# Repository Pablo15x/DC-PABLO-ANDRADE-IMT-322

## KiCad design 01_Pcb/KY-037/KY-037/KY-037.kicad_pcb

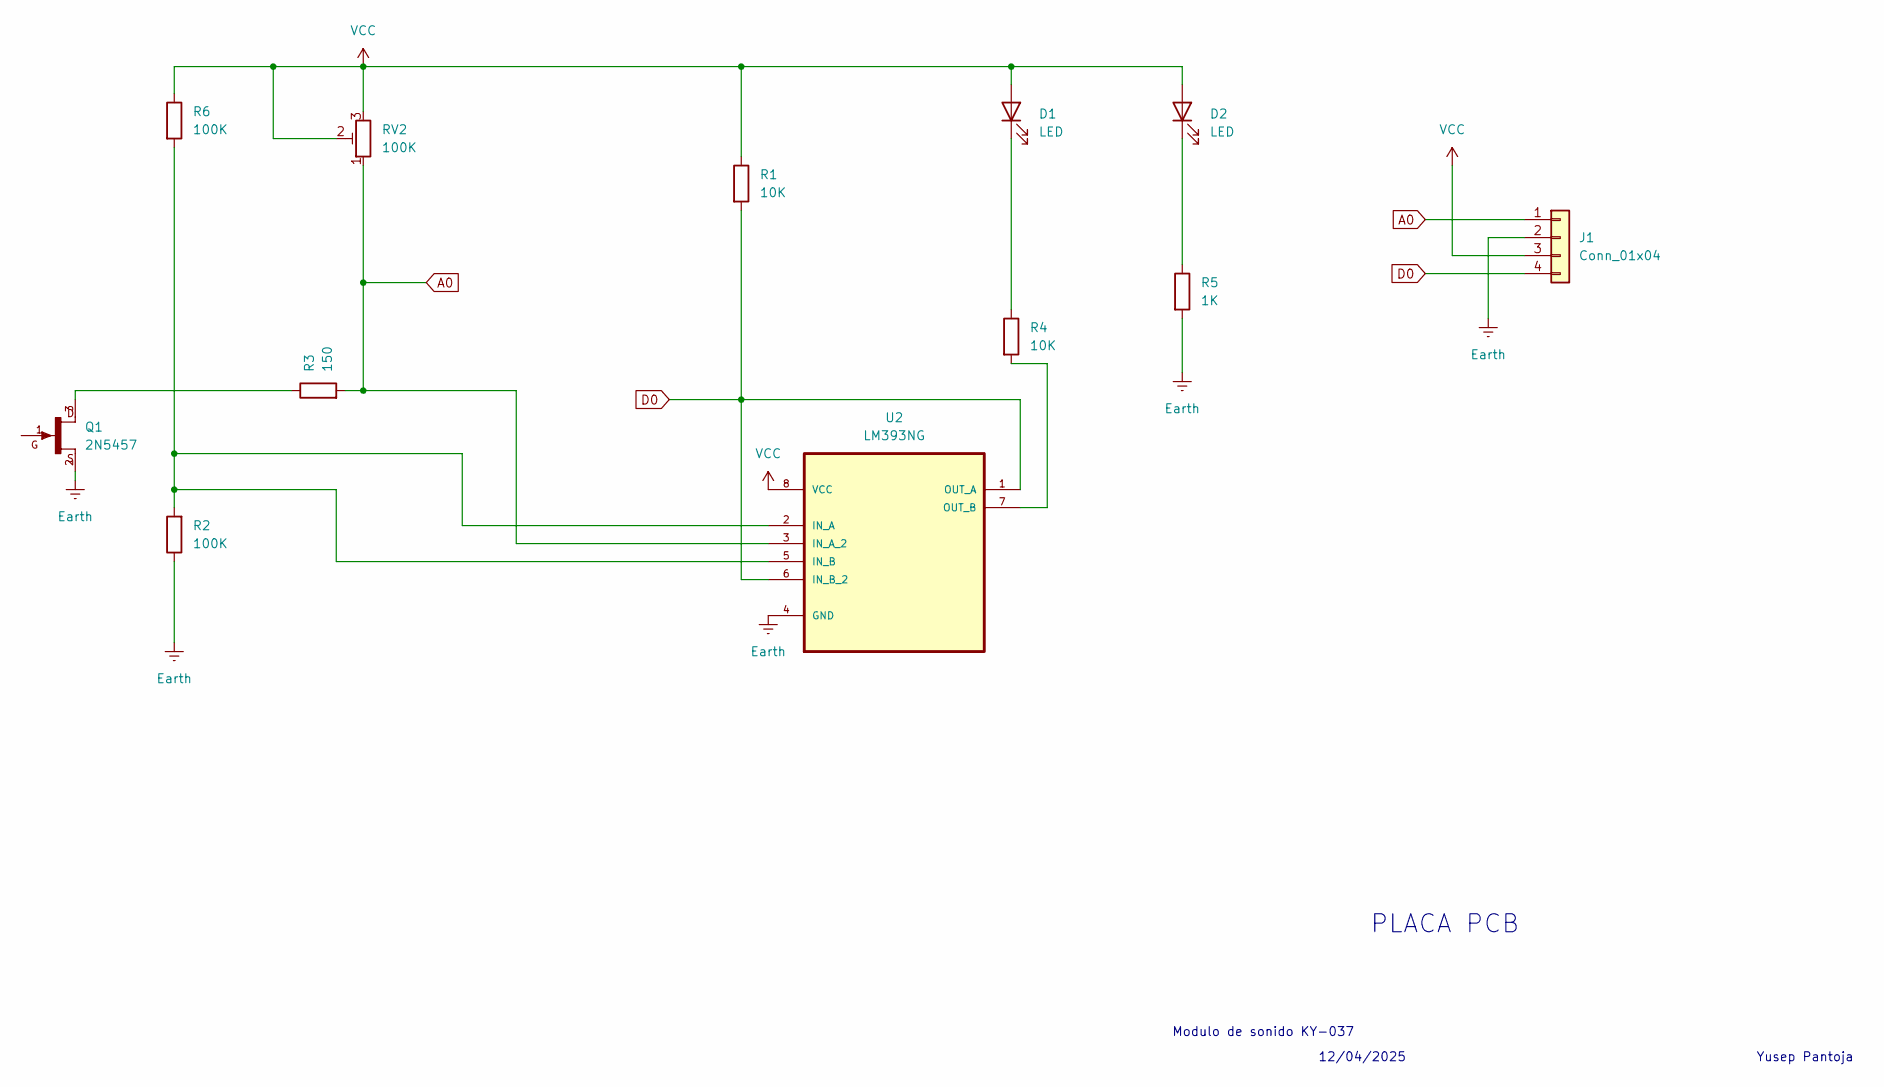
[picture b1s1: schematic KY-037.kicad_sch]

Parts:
D1, D2: LED; D_DO-35_SOD27_P7.62mm_Horizontal
J1: Conn_01x04; PinHeader_1x04_P2.54mm_Vertical
Q1: 2N5457; TO-92L_Inline
R1, R4: 10K; R_Axial_DIN0207_L6.3mm_D2.5mm_P7.62mm_Horizontal
R2, R6: 100K; R_Axial_DIN0207_L6.3mm_D2.5mm_P7.62mm_Horizontal
R3: 150; R_Axial_DIN0207_L6.3mm_D2.5mm_P7.62mm_Horizontal
R5: 1K; R_Axial_DIN0207_L6.3mm_D2.5mm_P7.62mm_Horizontal
RV2: 100K; Potentiometer_Bourns_3296W_Vertical
U2: LM393NG; CERDIP-8_W7.62mm_SideBrazed; MPN LM393NG

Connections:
A0: J1.1, R3.2, RV2.1, U2.3 (IN_A_2)
D0: J1.4, R1.2, U2.1 (OUT_A), U2.6 (IN_B_2)
Earth: J1.2, Q1.2, R2.1, R5.2, U2.4 (GND)
unnamed: D1.1 (K), R4.1
unnamed: D2.1 (K), R5.1
unnamed: Q1.3, R3.1
unnamed: R2.2, R6.2, U2.2 (IN_A), U2.5 (IN_B)
unnamed: R4.2, U2.7 (OUT_B)
VCC: D1.2 (A), D2.2 (A), J1.3, R1.1, R6.1, RV2.2, RV2.3, U2.8 (VCC)

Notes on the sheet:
PLACA PCB
12/04/2025
Modulo de sonido KY-037
Yusep Pantoja

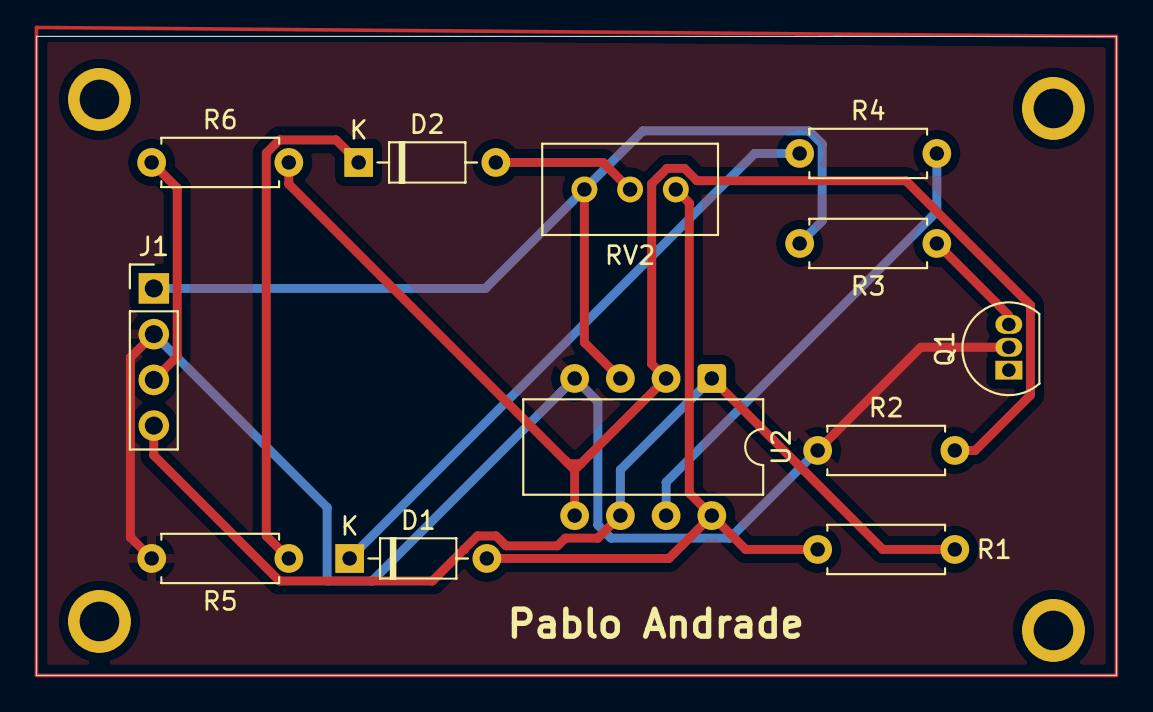
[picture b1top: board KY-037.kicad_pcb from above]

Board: 2 copper layers, 60.0 x 35.5 mm, 12 parts (0 on the bottom side), 9 nets.

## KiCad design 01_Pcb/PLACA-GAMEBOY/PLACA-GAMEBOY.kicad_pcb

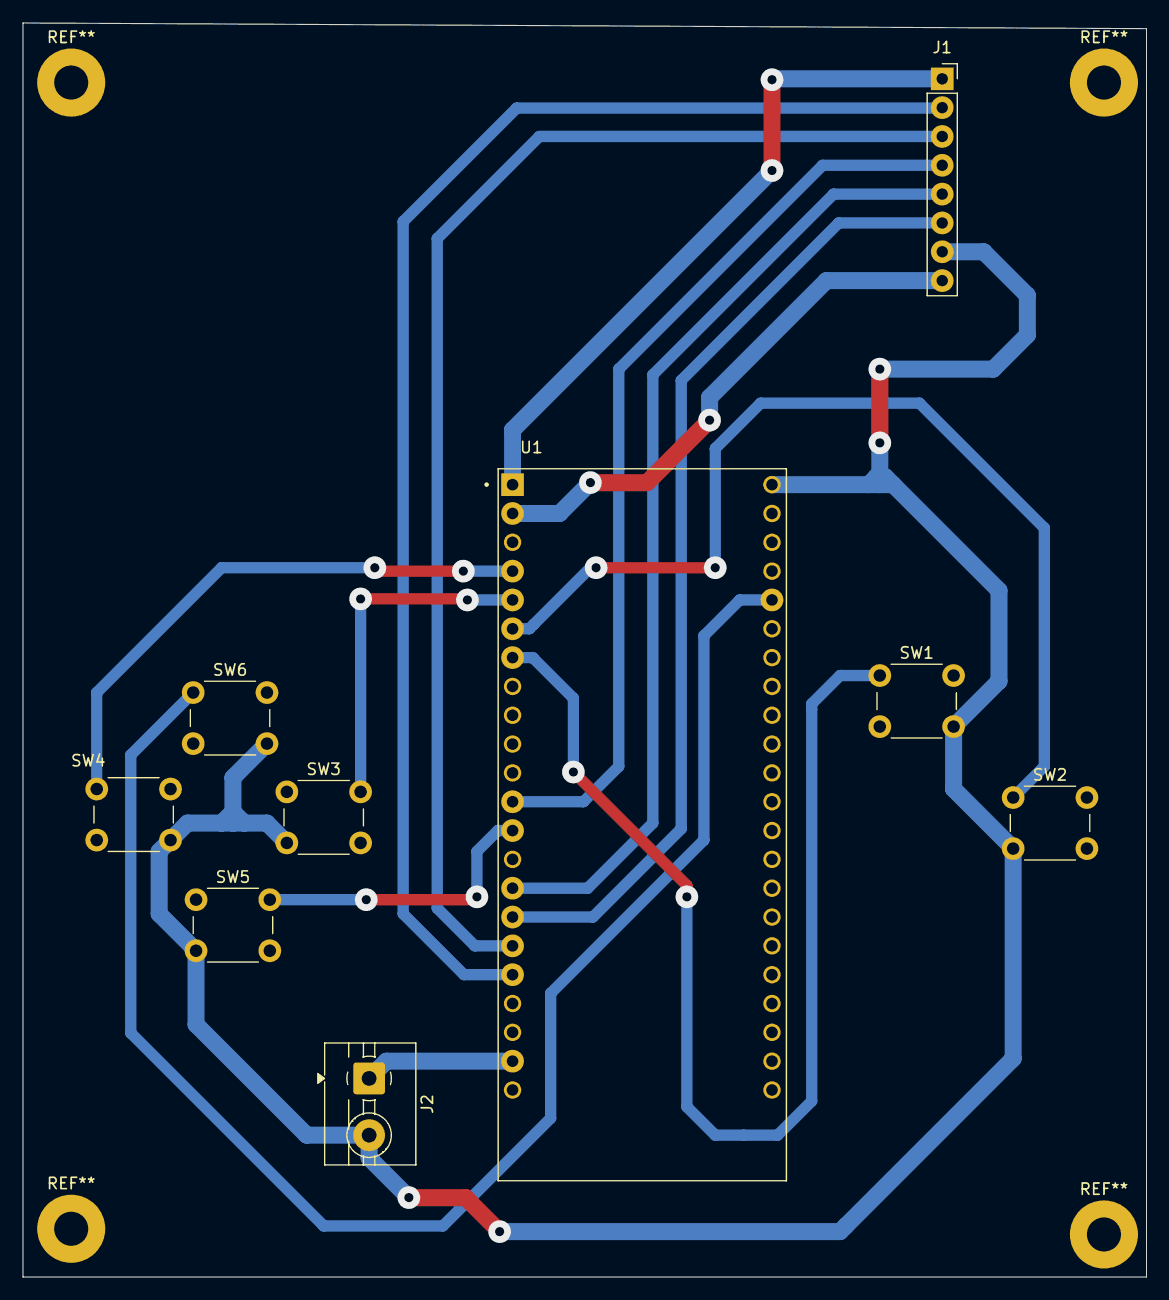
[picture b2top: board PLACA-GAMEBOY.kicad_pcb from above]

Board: 2 copper layers, 99.0 x 110.5 mm, 9 parts (0 on the bottom side), 15 nets.

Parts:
J1: Conn_01x08; PinSocket_1x08_P2.54mm_Vertical
J2: Conn_01x02_Socket; TerminalBlock_MaiXu_MX126-5.0-02P_1x02_P5.00mm
SW1, SW2, SW3, SW4, SW5, SW6: SW_Push; SW_PUSH_6mm_H4.3mm
U1: ESP32-S3-DEVKITC-1-N8R8

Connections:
unnamed: J1.1, U1.J1_1 (3V3)
unnamed: J1.2, U1.J1_18 (GPIO12)
unnamed: J1.3, U1.J1_17 (GPIO11)
unnamed: J1.4, U1.J1_12 (GPIO8)
unnamed: J1.5, U1.J1_15 (GPIO9)
unnamed: J1.6, U1.J1_16 (GPIO10)
unnamed: J1.7, J2.2, SW1.2, SW2.2, SW3.2, SW4.2, SW5.2, SW6.2, U1.J3_1 (GND)
unnamed: J1.8, U1.J1_2 (3V3.)
unnamed: J2.1, U1.J1_21 (5V0)
unnamed: SW6.1, U1.J3_5 (GPIO2)
unnamed: SW5.1, U1.J1_13 (GPIO3)
unnamed: SW4.1, U1.J1_4 (GPIO4)
unnamed: SW3.1, U1.J1_5 (GPIO5)
unnamed: SW2.1, U1.J1_6 (GPIO6)
unnamed: SW1.1, U1.J1_7 (GPIO7)

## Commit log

2025-03-11 template
2025-05-20 refresh
2025-05-29 document
